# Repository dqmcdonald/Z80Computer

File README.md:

# Z80Computer

Simple computer based on Z80 processor

D. Q. McDonald
May 2026

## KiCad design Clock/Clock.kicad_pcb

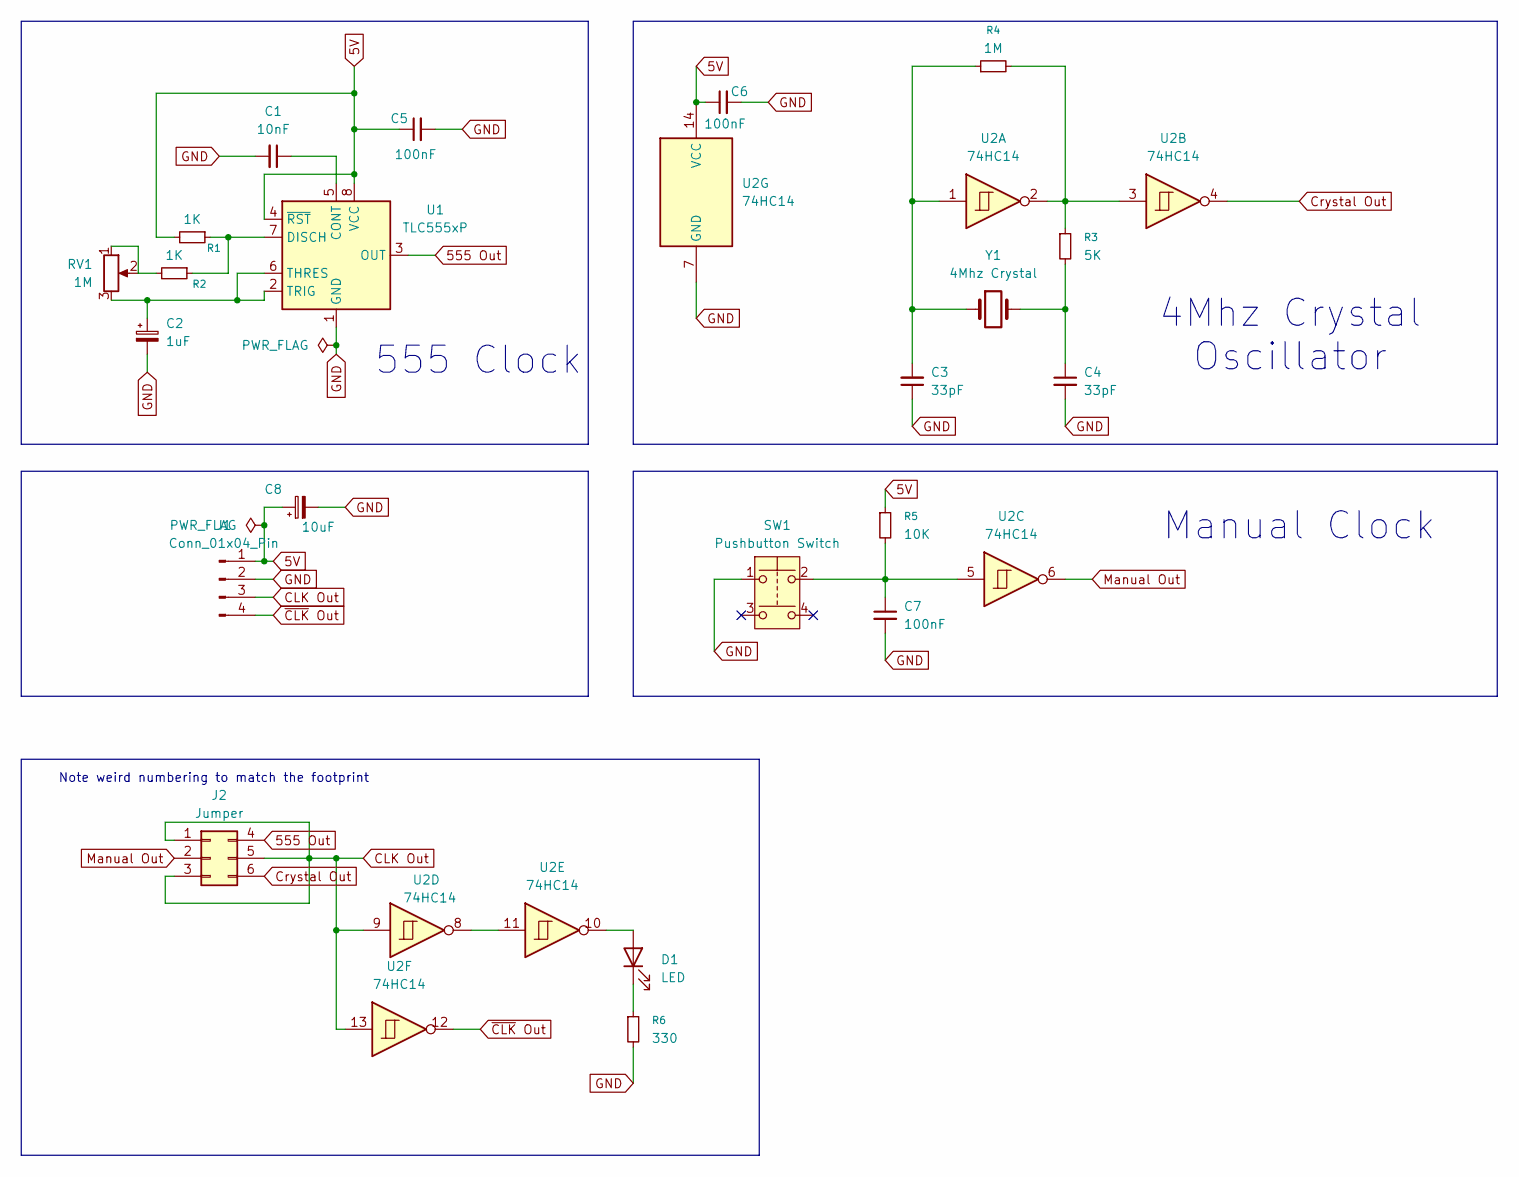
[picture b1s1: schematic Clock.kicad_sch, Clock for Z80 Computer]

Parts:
C1: 10nF; C_0805_2012Metric
C2: 1uF; C_0805_2012Metric
C3, C4: 33pF; C_0805_2012Metric
C5, C6, C7: 100nF; C_0805_2012Metric
C8: 10uF; C_0805_2012Metric
D1: LED; LED_0805_2012Metric_Pad1.15x1.40mm_HandSolder
J1: Conn_01x04_Pin; PinHeader_1x04_P2.54mm_Vertical
J2: Jumper; PinHeader_2x03_P2.54mm_Vertical
R1, R2: 1K; R_0805_2012Metric
R3: 5K; R_0805_2012Metric
R4: 1M; R_0805_2012Metric
R5: 10K; R_0805_2012Metric
R6: 330; R_0805_2012Metric_Pad1.20x1.40mm_HandSolder
RV1: 1M; Potentiometer_Bourns_3296W_Vertical
SW1: Pushbutton Switch; SW_PUSH_6mm
U1: TLC555xP; DIP-8_W7.62mm; MPN TLC555CP
U2: 74HC14; DIP-14_W7.62mm; MPN 74HC14N
Y1: 4Mhz Crystal; Crystal_HC49-U_Vertical

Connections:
5V: C5.1, C6.1, C8.1, J1.1, R1.2, R5.1, U1.4 (~RST), U1.8 (VCC), U2.14 (VCC)
555 Out: J2.4, U1.3 (OUT)
CLK Out: J1.3, J2.1, J2.3, J2.5, U2.9, U2.13
Crystal Out: J2.6, U2.4
GND: C1.2, C2.2, C3.1, C4.2, C5.2, C6.2, C7.2, C8.2, J1.2, R6.2, SW1.1, U1.1 (GND), U2.7 (GND)
Manual Out: J2.2, U2.6
unnamed: C3.2, R4.1, U2.1, Y1.1
unnamed: C4.1, R3.2, Y1.2
unnamed: C7.1, R5.2, SW1.2, U2.5
unnamed: D1.2 (A), U2.10
unnamed: D1.1 (K), R6.1
unnamed: R2.2, RV1.1, RV1.2
unnamed: R3.1, R4.2, U2.2, U2.3
unnamed: C1.1, U1.5 (CONT)
unnamed: R1.1, R2.1, U1.7 (DISCH)
unnamed: C2.1, RV1.3, U1.2 (TRIG), U1.6 (THRES)
unnamed: U2.8, U2.11
~CLK Out: J1.4, U2.12

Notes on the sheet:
555 Clock
Note weird numbering to match the footprint
Manual Clock
4Mhz Crystal Oscillator

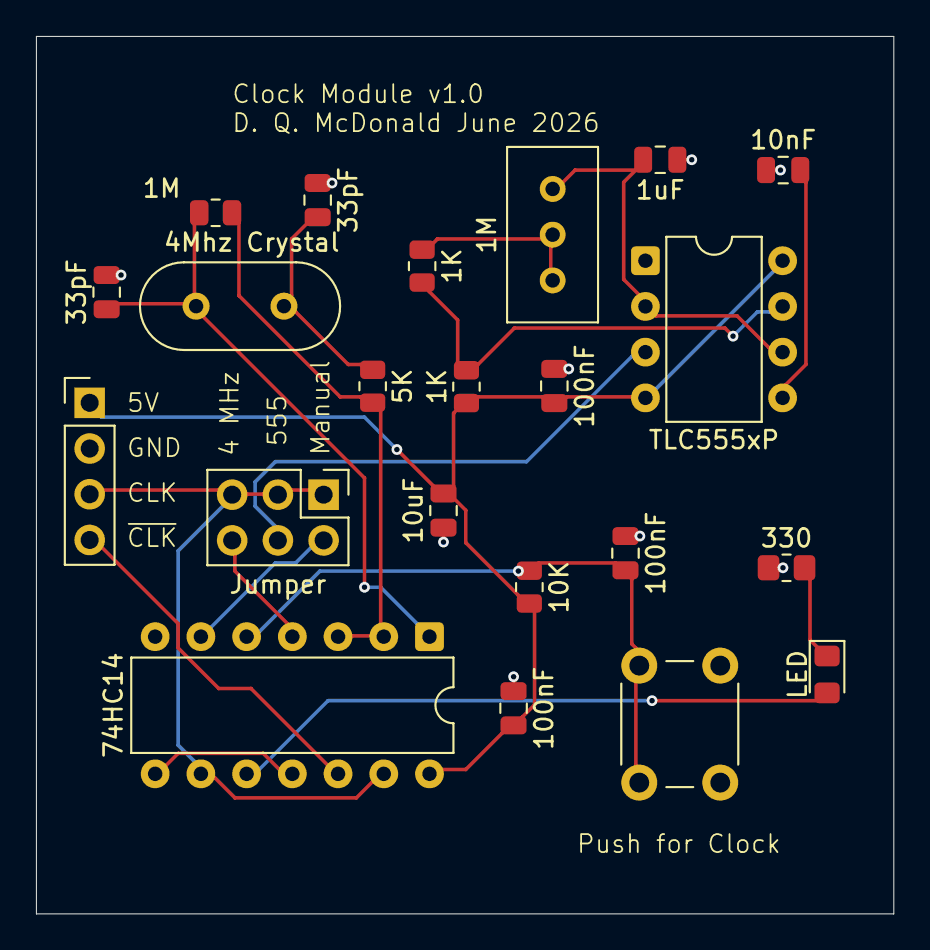
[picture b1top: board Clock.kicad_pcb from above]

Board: 2 copper layers, 47.6 x 48.7 mm, 22 parts (0 on the bottom side), 18 nets.

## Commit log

2026-06-03 Added first routed and reviewed version of Clock.
2026-06-05 [CLock] Some small changes to board text to make functions clearer.
